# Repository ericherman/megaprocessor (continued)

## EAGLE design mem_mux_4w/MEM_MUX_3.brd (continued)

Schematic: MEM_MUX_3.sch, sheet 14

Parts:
D25, D26, D27, D28, D29, D30, D31, D32: L-1334SRT; LED3MM
Q127, Q128, Q129, Q130, Q131, Q132, Q133, Q134, Q135, Q136, Q137, Q138, Q139, Q140, Q141, Q142: 2N7000; TO92-DGS
R151, R153, R155, R157, R159, R161, R163, R165, R167, R168, R169, R170, R171, R172, R173, R174: 10k; R_P2INCH
R152, R154, R156, R158, R160, R162, R164, R166: 470; R_P2INCH

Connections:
+5V: D25.A, D26.A, D27.A, D28.A, D29.A, D30.A, D31.A, D32.A, R151.2, R153.2, R155.2, R157.2, R159.2, R161.2, R163.2, R165.2, R167.2, R168.2, R169.2, R170.2, R171.2, R172.2, R173.2, R174.2; also elsewhere on the board
CS_3_N: Q128.S, Q130.S, Q132.S, Q134.S, Q136.S, Q138.S, Q140.S, Q142.S; also elsewhere on the board
GND: Q127.S, Q129.S, Q131.S, Q133.S, Q135.S, Q137.S, Q139.S, Q141.S; also elsewhere on the board
unnamed: Q127.D, Q128.G, R151.1, R152.1
unnamed: D25.K (C), R152.2
unnamed: Q129.D, Q130.G, R153.1, R154.1
unnamed: D26.K (C), R154.2
unnamed: Q131.D, Q132.G, R155.1, R156.1
unnamed: D27.K (C), R156.2
unnamed: Q133.D, Q134.G, R157.1, R158.1
unnamed: D28.K (C), R158.2
unnamed: Q135.D, Q136.G, R159.1, R160.1
unnamed: D29.K (C), R160.2
unnamed: Q137.D, Q138.G, R161.1, R162.1
unnamed: D30.K (C), R162.2
unnamed: Q139.D, Q140.G, R163.1, R164.1
unnamed: D31.K (C), R164.2
unnamed: Q141.D, Q142.G, R165.1, R166.1
unnamed: D32.K (C), R166.2
P3_RD0: Q127.G; also elsewhere on the board
P3_RD0_B: Q128.D, R167.1; also elsewhere on the board
P3_RD1: Q129.G; also elsewhere on the board
P3_RD1_B: Q130.D, R168.1; also elsewhere on the board
P3_RD2: Q131.G; also elsewhere on the board
P3_RD2_B: Q132.D, R169.1; also elsewhere on the board
P3_RD3: Q133.G; also elsewhere on the board
P3_RD3_B: Q134.D, R170.1; also elsewhere on the board
P3_RD4: Q135.G; also elsewhere on the board
P3_RD4_B: Q136.D, R171.1; also elsewhere on the board
P3_RD5: Q137.G; also elsewhere on the board
P3_RD5_B: Q138.D, R172.1; also elsewhere on the board
P3_RD6: Q139.G; also elsewhere on the board
P3_RD6_B: Q140.D, R173.1; also elsewhere on the board
P3_RD7: Q141.G; also elsewhere on the board
P3_RD7_B: Q142.D, R174.1; also elsewhere on the board

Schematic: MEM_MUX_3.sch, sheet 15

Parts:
J7, J8: 20_HDR_LOCKING_RA
Q143, Q144: 2N7000; TO92-DGS
R175, R176: 10k; R_P2INCH

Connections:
+5V: R175.2, R176.2; also elsewhere on the board
GND: J7.1, J7.10, J7.11, J7.20, J8.2, J8.4, Q143.S, Q144.S; also elsewhere on the board
P3_A0: J8.5; also elsewhere on the board
P3_A1: J8.6; also elsewhere on the board
P3_A2: J8.7; also elsewhere on the board
P3_A3: J8.8; also elsewhere on the board
P3_A4: J8.9; also elsewhere on the board
P3_A5: J8.10; also elsewhere on the board
P3_A6: J8.11; also elsewhere on the board
P3_A7: J8.12; also elsewhere on the board
P3_A8: J8.13; also elsewhere on the board
P3_A9: J8.14; also elsewhere on the board
P3_A10: J8.15; also elsewhere on the board
P3_A11: J8.16; also elsewhere on the board
P3_A12: J8.17; also elsewhere on the board
P3_A13: J8.18; also elsewhere on the board
P3_A14: J8.19; also elsewhere on the board
P3_A15: J8.20; also elsewhere on the board
P3_CS: Q143.G; also elsewhere on the board
P3_CS_N: J8.1, Q143.D, R175.1
P3_RD0: J7.2; also elsewhere on the board
P3_RD1: J7.3; also elsewhere on the board
P3_RD2: J7.4; also elsewhere on the board
P3_RD3: J7.5; also elsewhere on the board
P3_RD4: J7.6; also elsewhere on the board
P3_RD5: J7.7; also elsewhere on the board
P3_RD6: J7.8; also elsewhere on the board
P3_RD7: J7.9; also elsewhere on the board
P3_WD0: J7.12; also elsewhere on the board
P3_WD1: J7.13; also elsewhere on the board
P3_WD2: J7.14; also elsewhere on the board
P3_WD3: J7.15; also elsewhere on the board
P3_WD4: J7.16; also elsewhere on the board
P3_WD5: J7.17; also elsewhere on the board
P3_WD6: J7.18; also elsewhere on the board
P3_WD7: J7.19; also elsewhere on the board
P3_WE_N: J8.3, Q144.D, R176.1
WE: Q144.G; also elsewhere on the board

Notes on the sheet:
Port 1 data
Port 1 address
rd data
wr_data

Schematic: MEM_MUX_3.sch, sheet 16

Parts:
Q145, Q146, Q147, Q148, Q149, Q150, Q151, Q152, Q153, Q154, Q155, Q156, Q157, Q158, Q159, Q160, Q161, Q162, Q163, Q164, Q165, Q166, Q167, Q168: 2N7000; TO92-DGS
R177, R178, R179, R180, R181, R182, R183, R184, R185, R186, R187, R188, R189, R190, R191, R192, R193, R194, R195, R196, R197, R198, R199, R200: 10k; R_P2INCH

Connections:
+5V: R177.2, R178.2, R179.2, R180.2, R181.2, R182.2, R183.2, R184.2, R185.2, R186.2, R187.2, R188.2, R189.2, R190.2, R191.2, R192.2, R193.2, R194.2, R195.2, R196.2, R197.2, R198.2, R199.2, R200.2; also elsewhere on the board
A0_N: Q153.G; also elsewhere on the board
A1_N: Q154.G; also elsewhere on the board
A2_N: Q155.G; also elsewhere on the board
A3_N: Q156.G; also elsewhere on the board
A4_N: Q157.G; also elsewhere on the board
A5_N: Q158.G; also elsewhere on the board
A6_N: Q159.G; also elsewhere on the board
A7_N: Q160.G; also elsewhere on the board
A8_N: Q161.G; also elsewhere on the board
A9_N: Q162.G; also elsewhere on the board
A10_N: Q163.G; also elsewhere on the board
A11_N: Q164.G; also elsewhere on the board
A12_N: Q165.G; also elsewhere on the board
A13_N: Q166.G; also elsewhere on the board
A14_N: Q167.G; also elsewhere on the board
A15_N: Q168.G; also elsewhere on the board
GND: Q145.S, Q146.S, Q147.S, Q148.S, Q149.S, Q150.S, Q151.S, Q152.S, Q153.S, Q154.S, Q155.S, Q156.S, Q157.S, Q158.S, Q159.S, Q160.S, Q161.S, Q162.S, Q163.S, Q164.S, Q165.S, Q166.S, Q167.S, Q168.S; also elsewhere on the board
P3_A0: Q153.D, R185.1; also elsewhere on the board
P3_A1: Q154.D, R186.1; also elsewhere on the board
P3_A2: Q155.D, R187.1; also elsewhere on the board
P3_A3: Q156.D, R188.1; also elsewhere on the board
P3_A4: Q157.D, R189.1; also elsewhere on the board
P3_A5: Q158.D, R190.1; also elsewhere on the board
P3_A6: Q159.D, R191.1; also elsewhere on the board
P3_A7: Q160.D, R192.1; also elsewhere on the board
P3_A8: Q161.D, R193.1; also elsewhere on the board
P3_A9: Q162.D, R194.1; also elsewhere on the board
P3_A10: Q163.D, R195.1; also elsewhere on the board
P3_A11: Q164.D, R196.1; also elsewhere on the board
P3_A12: Q165.D, R197.1; also elsewhere on the board
P3_A13: Q166.D, R198.1; also elsewhere on the board
P3_A14: Q167.D, R199.1; also elsewhere on the board
P3_A15: Q168.D, R200.1; also elsewhere on the board
P3_WD0: Q145.D, R177.1; also elsewhere on the board
P3_WD1: Q146.D, R178.1; also elsewhere on the board
P3_WD2: Q147.D, R179.1; also elsewhere on the board
P3_WD3: Q148.D, R180.1; also elsewhere on the board
P3_WD4: Q149.D, R181.1; also elsewhere on the board
P3_WD5: Q150.D, R182.1; also elsewhere on the board
P3_WD6: Q151.D, R183.1; also elsewhere on the board
P3_WD7: Q152.D, R184.1; also elsewhere on the board
WD0_N: Q145.G; also elsewhere on the board
WD1_N: Q146.G; also elsewhere on the board
WD2_N: Q147.G; also elsewhere on the board
WD3_N: Q148.G; also elsewhere on the board
WD4_N: Q149.G; also elsewhere on the board
WD5_N: Q150.G; also elsewhere on the board
WD6_N: Q151.G; also elsewhere on the board
WD7_N: Q152.G; also elsewhere on the board

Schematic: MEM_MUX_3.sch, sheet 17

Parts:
D33, D34, D35, D69: L-1334SRT; LED3MM
Q169, Q170, Q171, Q172, Q173, Q174, Q175, Q176, Q177, Q178, Q179, Q180, Q181, Q182, Q183, Q184, Q185, Q186, Q187, Q188: 2N7000; TO92-DGS
R201, R203, R205, R207, R257, R258, R259, R260: 10k; R_P2INCH
R202, R204, R206, R208: 470; R_P2INCH

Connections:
+5V: D33.A, D34.A, D35.A, D69.A, R201.2, R203.2, R205.2, R207.2, R257.2, R258.2, R259.2, R260.2; also elsewhere on the board
GND: Q170.S, Q173.S, Q175.S, Q178.S, Q180.S, Q183.S, Q185.S, Q188.S; also elsewhere on the board
unnamed: Q174.D, Q175.G, R203.1, R204.1
unnamed: D33.K (C), R204.2
unnamed: Q177.S, Q178.D
unnamed: Q176.S, Q177.D
unnamed: Q174.S, Q176.D
unnamed: Q179.D, Q180.G, R205.1, R206.1
unnamed: D34.K (C), R206.2
unnamed: Q182.S, Q183.D
unnamed: Q181.S, Q182.D
unnamed: Q179.S, Q181.D
unnamed: Q184.D, Q185.G, R207.1, R208.1
unnamed: D35.K (C), R208.2
unnamed: Q187.S, Q188.D
unnamed: Q186.S, Q187.D
unnamed: Q184.S, Q186.D
unnamed: Q169.D, Q170.G, R201.1, R202.1
unnamed: D69.K (C), R202.2
unnamed: Q172.S, Q173.D
unnamed: Q171.S, Q172.D
unnamed: Q169.S, Q171.D
P0_RD0_B: Q169.G; also elsewhere on the board
P0_RD1_B: Q174.G; also elsewhere on the board
P0_RD2_B: Q179.G; also elsewhere on the board
P0_RD3_B: Q184.G; also elsewhere on the board
P1_RD0_B: Q171.G; also elsewhere on the board
P1_RD1_B: Q176.G; also elsewhere on the board
P1_RD2_B: Q181.G; also elsewhere on the board
P1_RD3_B: Q186.G; also elsewhere on the board
P2_RD0_B: Q172.G; also elsewhere on the board
P2_RD1_B: Q177.G; also elsewhere on the board
P2_RD2_B: Q182.G; also elsewhere on the board
P2_RD3_B: Q187.G; also elsewhere on the board
P3_RD0_B: Q173.G; also elsewhere on the board
P3_RD1_B: Q178.G; also elsewhere on the board
P3_RD2_B: Q183.G; also elsewhere on the board
P3_RD3_B: Q188.G; also elsewhere on the board
RD0: Q170.D, R257.1; also elsewhere on the board
RD1: Q175.D, R258.1; also elsewhere on the board
RD2: Q180.D, R259.1; also elsewhere on the board
RD3: Q185.D, R260.1; also elsewhere on the board

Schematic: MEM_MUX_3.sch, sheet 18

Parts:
D36, D37, D38, D39: L-1334SRT; LED3MM
Q189, Q190, Q191, Q192, Q193, Q194, Q195, Q196, Q197, Q198, Q199, Q200, Q201, Q202, Q203, Q204, Q205, Q206, Q207, Q208: 2N7000; TO92-DGS
R209, R211, R213, R215, R253, R254, R255, R256: 10k; R_P2INCH
R210, R212, R214, R216: 470; R_P2INCH

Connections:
+5V: D36.A, D37.A, D38.A, D39.A, R209.2, R211.2, R213.2, R215.2, R253.2, R254.2, R255.2, R256.2; also elsewhere on the board
GND: Q190.S, Q193.S, Q195.S, Q198.S, Q200.S, Q203.S, Q205.S, Q208.S; also elsewhere on the board
unnamed: Q189.D, Q190.G, R209.1, R210.1
unnamed: D36.K (C), R210.2
unnamed: Q192.S, Q193.D
unnamed: Q191.S, Q192.D
unnamed: Q189.S, Q191.D
unnamed: Q194.D, Q195.G, R211.1, R212.1
unnamed: D37.K (C), R212.2
unnamed: Q197.S, Q198.D
unnamed: Q196.S, Q197.D
unnamed: Q194.S, Q196.D
unnamed: Q199.D, Q200.G, R213.1, R214.1
unnamed: D38.K (C), R214.2
unnamed: Q202.S, Q203.D
unnamed: Q201.S, Q202.D
unnamed: Q199.S, Q201.D
unnamed: Q204.D, Q205.G, R215.1, R216.1
unnamed: D39.K (C), R216.2
unnamed: Q207.S, Q208.D
unnamed: Q206.S, Q207.D
unnamed: Q204.S, Q206.D
P0_RD4_B: Q189.G; also elsewhere on the board
P0_RD5_B: Q194.G; also elsewhere on the board
P0_RD6_B: Q199.G; also elsewhere on the board
P0_RD7_B: Q204.G; also elsewhere on the board
P1_RD4_B: Q191.G; also elsewhere on the board
P1_RD5_B: Q196.G; also elsewhere on the board
P1_RD6_B: Q201.G; also elsewhere on the board
P1_RD7_B: Q206.G; also elsewhere on the board
P2_RD4_B: Q192.G; also elsewhere on the board
P2_RD5_B: Q197.G; also elsewhere on the board
P2_RD6_B: Q202.G; also elsewhere on the board
P2_RD7_B: Q207.G; also elsewhere on the board
P3_RD4_B: Q193.G; also elsewhere on the board
P3_RD5_B: Q198.G; also elsewhere on the board
P3_RD6_B: Q203.G; also elsewhere on the board
P3_RD7_B: Q208.G; also elsewhere on the board
RD4: Q190.D, R253.1; also elsewhere on the board
RD5: Q195.D, R254.1; also elsewhere on the board
RD6: Q200.D, R255.1; also elsewhere on the board
RD7: Q205.D, R256.1; also elsewhere on the board

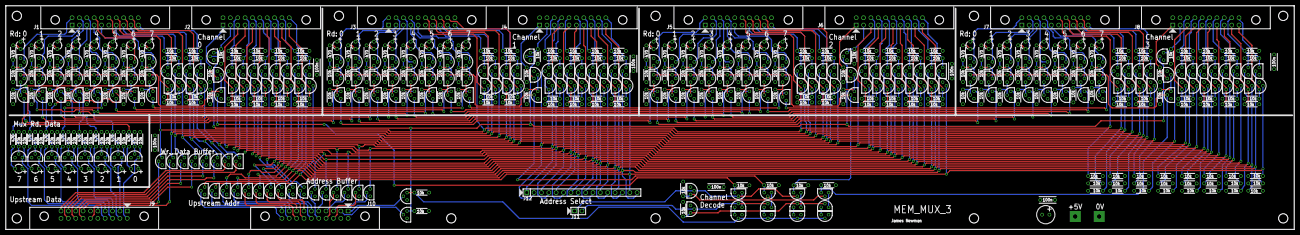
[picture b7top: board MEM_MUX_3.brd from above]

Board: 4 copper layers, 444.5 x 77.1 mm, 584 parts (0 on the bottom side), 354 nets.

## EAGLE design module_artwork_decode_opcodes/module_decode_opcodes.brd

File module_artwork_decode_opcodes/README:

Opcode Decode

This decodes the opcode to work out what the instruction is.

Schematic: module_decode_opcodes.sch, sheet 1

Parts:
CMP13, CMP14, CMP15, CMP17, CMP49: BUS_SPLIT_DISPLAY

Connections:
ADD2_IS_Z: CMP49.P$11 (OUT_10)
ADD2_LSB: CMP49.P$12 (OUT_11)
BUS_H_D: CMP14.INPUT
BUS_INSTR: CMP15.INPUT
BUS_PS: CMP17.INPUT
BUS_RN_ARITH_FLAGS: CMP49.INPUT
BUS_STATE: CMP13.INPUT
FLAG_C: CMP17.P$6 (OUT_5)
FLAG_D: CMP17.P$7 (OUT_6)
FLAG_F0: CMP17.P$9 (OUT_8)
FLAG_F1: CMP17.P$10 (OUT_9)
FLAG_F2: CMP17.P$11 (OUT_10)
FLAG_F3: CMP17.P$12 (OUT_11)
FLAG_F4: CMP17.P$13 (OUT_12)
FLAG_F5: CMP17.P$14 (OUT_13)
FLAG_F6: CMP17.P$15 (OUT_14); also elsewhere on the board
FLAG_I: CMP17.P$1 (OUT_0); also elsewhere on the board
FLAG_N: CMP17.P$2 (OUT_1)
FLAG_V: CMP17.P$4 (OUT_3)
FLAG_X: CMP17.P$5 (OUT_4)
FLAG_Z: CMP17.P$3 (OUT_2)
H_0: CMP14.P$1 (OUT_0); also elsewhere on the board
H_1: CMP14.P$2 (OUT_1); also elsewhere on the board
H_2: CMP14.P$3 (OUT_2); also elsewhere on the board
H_3: CMP14.P$4 (OUT_3); also elsewhere on the board
H_4: CMP14.P$5 (OUT_4); also elsewhere on the board
H_5: CMP14.P$6 (OUT_5)
H_6: CMP14.P$7 (OUT_6); also elsewhere on the board
H_7: CMP14.P$8 (OUT_7); also elsewhere on the board
H_8: CMP14.P$9 (OUT_8)
H_9: CMP14.P$10 (OUT_9)
H_10: CMP14.P$11 (OUT_10)
H_11: CMP14.P$12 (OUT_11)
H_12: CMP14.P$13 (OUT_12)
H_13: CMP14.P$14 (OUT_13)
H_14: CMP14.P$15 (OUT_14)
H_15: CMP14.P$16 (OUT_15)
INSTR_0: CMP15.P$1 (OUT_0); also elsewhere on the board
INSTR_0_N: CMP15.P$9 (OUT_8)
INSTR_1: CMP15.P$2 (OUT_1); also elsewhere on the board
INSTR_1_N: CMP15.P$10 (OUT_9)
INSTR_2: CMP15.P$3 (OUT_2); also elsewhere on the board
INSTR_2_N: CMP15.P$11 (OUT_10); also elsewhere on the board
INSTR_3: CMP15.P$4 (OUT_3); also elsewhere on the board
INSTR_3_N: CMP15.P$12 (OUT_11); also elsewhere on the board
INSTR_4: CMP15.P$5 (OUT_4); also elsewhere on the board
INSTR_4_N: CMP15.P$13 (OUT_12)
INSTR_5: CMP15.P$6 (OUT_5); also elsewhere on the board
INSTR_5_N: CMP15.P$14 (OUT_13)
INSTR_6: CMP15.P$7 (OUT_6); also elsewhere on the board
INSTR_6_N: CMP15.P$15 (OUT_14); also elsewhere on the board
INSTR_7: CMP15.P$8 (OUT_7); also elsewhere on the board
INSTR_7_N: CMP15.P$16 (OUT_15); also elsewhere on the board
MAIN_RN_INPUT_MUX_IS_N: CMP49.P$9 (OUT_8)
MAIN_RN_INPUT_MUX_IS_Z: CMP49.P$10 (OUT_9)
R0_IS_N: CMP49.P$1 (OUT_0)
R0_IS_Z: CMP49.P$5 (OUT_4)
R1_IS_N: CMP49.P$2 (OUT_1)
R1_IS_Z: CMP49.P$6 (OUT_5); also elsewhere on the board
R2_IS_N: CMP49.P$3 (OUT_2)
R2_IS_Z: CMP49.P$7 (OUT_6)
R3_IS_N: CMP49.P$4 (OUT_3)
R3_IS_Z: CMP49.P$8 (OUT_7)
STATE_0: CMP13.P$1 (OUT_0); also elsewhere on the board
STATE_1: CMP13.P$2 (OUT_1); also elsewhere on the board
STATE_2: CMP13.P$3 (OUT_2); also elsewhere on the board
STATE_3: CMP13.P$4 (OUT_3); also elsewhere on the board
STATE_4: CMP13.P$5 (OUT_4)
STATE_5: CMP13.P$6 (OUT_5); also elsewhere on the board
STATE_6: CMP13.P$7 (OUT_6)
STATE_7: CMP13.P$8 (OUT_7); also elsewhere on the board
STATE_8: CMP13.P$9 (OUT_8)
STATE_9: CMP13.P$10 (OUT_9)
STATE_10: CMP13.P$11 (OUT_10)
STATE_11: CMP13.P$12 (OUT_11)
STATE_12: CMP13.P$13 (OUT_12)
STATE_13: CMP13.P$14 (OUT_13)
STATE_14: CMP13.P$15 (OUT_14)
STATE_15: CMP13.P$16 (OUT_15)

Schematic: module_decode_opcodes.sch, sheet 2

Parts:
CMP21, CMP22: DECODER16

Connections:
INSTR_0: CMP22.A0; also elsewhere on the board
INSTR_1: CMP22.A1; also elsewhere on the board
INSTR_2: CMP22.A2; also elsewhere on the board
INSTR_3: CMP22.A3; also elsewhere on the board
INSTR_4: CMP21.A0; also elsewhere on the board
INSTR_5: CMP21.A1; also elsewhere on the board
INSTR_6: CMP21.A2; also elsewhere on the board
INSTR_7: CMP21.A3; also elsewhere on the board
OPCODE_IS_ABSOLUTE_GROUP: CMP21.P11; also elsewhere on the board
OPCODE_IS_ADDQ_GROUP: CMP21.P5; also elsewhere on the board
OPCODE_IS_ADDX: CMP22.P12; also elsewhere on the board
OPCODE_IS_ADD_GROUP: CMP21.P4; also elsewhere on the board
OPCODE_IS_ADD_SP: CMP22.P6; also elsewhere on the board
OPCODE_IS_ANDI_PS: CMP22.P4; also elsewhere on the board
OPCODE_IS_AND_GROUP: CMP21.P1; also elsewhere on the board
OPCODE_IS_BRANCH_GROUP: CMP21.P14; also elsewhere on the board
OPCODE_IS_CMP_GROUP: CMP21.P7; also elsewhere on the board
OPCODE_IS_DIVS: CMP22.P11; also elsewhere on the board
OPCODE_IS_DIVU: CMP22.P10; also elsewhere on the board
OPCODE_IS_IMMEDIATE_GROUP: CMP21.P13; also elsewhere on the board
OPCODE_IS_INDIRECT_GROUP: CMP21.P8; also elsewhere on the board
OPCODE_IS_JMP_ABS: CMP22.P3; also elsewhere on the board
OPCODE_IS_JMP_R0: CMP22.P2; also elsewhere on the board
OPCODE_IS_MISC_GROUP: CMP21.P15, CMP22.E
OPCODE_IS_MOVER_GROUP: CMP21.P0
OPCODE_IS_MOVE_R0_SP: CMP22.P0; also elsewhere on the board
OPCODE_IS_MOVE_SP_R0: CMP22.P1; also elsewhere on the board
OPCODE_IS_MULS: CMP22.P9; also elsewhere on the board
OPCODE_IS_MULU: CMP22.P8; also elsewhere on the board
OPCODE_IS_NEGX: CMP22.P14; also elsewhere on the board
OPCODE_IS_NOP_1: CMP22.P15; also elsewhere on the board
OPCODE_IS_ORI_PS: CMP22.P5; also elsewhere on the board
OPCODE_IS_OR_GROUP: CMP21.P3; also elsewhere on the board
OPCODE_IS_POSTINC_GROUP: CMP21.P9; also elsewhere on the board
OPCODE_IS_SQRT: CMP22.P7; also elsewhere on the board
OPCODE_IS_STACK_GROUP: CMP21.P12; also elsewhere on the board
OPCODE_IS_STACK_REL_GROUP: CMP21.P10; also elsewhere on the board
OPCODE_IS_SUBX: CMP22.P13; also elsewhere on the board
OPCODE_IS_SUB_GROUP: CMP21.P6; also elsewhere on the board
OPCODE_IS_XOR_GROUP: CMP21.P2; also elsewhere on the board

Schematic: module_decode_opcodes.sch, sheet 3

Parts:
CMP59, CMP60: DECODER16

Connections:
INSTR_0: CMP59.A0; also elsewhere on the board
INSTR_1: CMP59.A1; also elsewhere on the board
INSTR_2: CMP59.A2; also elsewhere on the board
INSTR_3: CMP59.A3; also elsewhere on the board
INSTR_4: CMP60.A0; also elsewhere on the board
INSTR_5: CMP60.A1; also elsewhere on the board
INSTR_6: CMP60.A2; also elsewhere on the board
INSTR_7_N: CMP60.E; also elsewhere on the board
OPCODE_IS_ABS: CMP60.P15; also elsewhere on the board
OPCODE_IS_AND: CMP60.P1
OPCODE_IS_CMP: CMP60.P7; also elsewhere on the board
OPCODE_IS_INV: CMP60.P11; also elsewhere on the board
OPCODE_IS_JSR_ABS: CMP59.P15; also elsewhere on the board
OPCODE_IS_JSR_R0: CMP59.P14; also elsewhere on the board
OPCODE_IS_MOVER: CMP60.P0; also elsewhere on the board
OPCODE_IS_NEG: CMP60.P14; also elsewhere on the board
OPCODE_IS_NOP_2: CMP59.P5; also elsewhere on the board
OPCODE_IS_OR: CMP60.P3; also elsewhere on the board
OPCODE_IS_POP_PS: CMP59.P4; also elsewhere on the board
OPCODE_IS_PUSH_PS: CMP59.P12; also elsewhere on the board
OPCODE_IS_RET: CMP59.P6; also elsewhere on the board
OPCODE_IS_RETI: CMP59.P7; also elsewhere on the board
OPCODE_IS_STACK_GROUP: CMP59.E; also elsewhere on the board
OPCODE_IS_SUB: CMP60.P6; also elsewhere on the board
OPCODE_IS_SXT: CMP60.P8; also elsewhere on the board
OPCODE_IS_TEST: CMP60.P9; also elsewhere on the board
OPCODE_IS_TRAP: CMP59.P13; also elsewhere on the board
RA_EQUALS_RB: CMP60.A3; also elsewhere on the board

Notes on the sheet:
alu_select_enable = ~bus_f_instr.instr[7];
alu_select[0] = bus_f_instr.instr[4]; alu_select[1] = bus_f_instr.instr[5]; alu_select[2] = bus_f_instr.instr[6]; alu_select[3] = RA_equals_RB;

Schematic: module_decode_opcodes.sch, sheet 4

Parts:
CMP1, CMP2: XOR
CMP3, CMP69, CMP72: 2AND
CMP23: 2OR
CMP67, CMP94: DECODER4

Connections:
INSTR_0: CMP1.P$1 (A1); also elsewhere on the board
INSTR_1: CMP2.P$1 (A1); also elsewhere on the board
INSTR_2: CMP1.P$2 (A2), CMP67.A0, CMP94.A0; also elsewhere on the board
INSTR_3: CMP2.P$2 (A2), CMP67.A1, CMP72.P$1 (1), CMP94.A1; also elsewhere on the board
INSTR_3_N: CMP69.P$1 (1); also elsewhere on the board
INSTR_6: CMP23.P$2 (A1); also elsewhere on the board
INSTR_7: CMP23.P$1 (A2); also elsewhere on the board
unnamed: CMP1.OUT_N (N), CMP3.P$2 (2)
unnamed: CMP2.OUT_N (N), CMP3.P$1 (1)
OPCODE_IS_BIT_XX: CMP67.P3; also elsewhere on the board
OPCODE_IS_BIT_XX_N: CMP67.N3; also elsewhere on the board
OPCODE_IS_IMMEDIATE_GROUP: CMP67.E, CMP69.P$2 (2), CMP72.P$2 (2); also elsewhere on the board
OPCODE_IS_LDI_X: CMP69.OUT_P; also elsewhere on the board
OPCODE_IS_LOGIC_GROUP: CMP23.OUT_M (N); also elsewhere on the board
OPCODE_IS_POP_RA: CMP94.P0; also elsewhere on the board
OPCODE_IS_PUSH_RA: CMP94.P2; also elsewhere on the board
OPCODE_IS_SHIFT_BIT: CMP72.OUT_P; also elsewhere on the board
OPCODE_IS_SHIFT_XX: CMP67.P2; also elsewhere on the board
OPCODE_IS_STACK_GROUP: CMP94.E; also elsewhere on the board
RA_EQUALS_RB: CMP3.OUT_P; also elsewhere on the board
RA_EQUALS_RB_N: CMP3.OUT_M (N)

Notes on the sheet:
RA0_equals_RB0 = ~Cpnt_XOR(RA_bits.Output()[0], RB_bits.Output()[0]); RA1_equals_RB1 = ~Cpnt_XOR(RA_bits.Output()[1], RB_bits.Output()[1]); RA_equals_RB = Cpnt_2AND(RA0_equals_RB0,RA1_equals_RB1);
opcode_is_logic_group = ~Cpnt_2OR(bus_f_instr.instr[7], bus_f_instr.instr[6]);
opcode_is_pop_ra = stack_decode.Output()[0]; opcode_is_push_ra = stack_decode.Output()[2];
opcode_is_ldi_x = Cpnt_2AND(opcode_is_immediate_group, ~bus_f_instr.instr[3]);
opcode_is_shift_bit = Cpnt_2AND(opcode_is_immediate_group, bus_f_instr.instr[3]);
opcode_is_shift_xx = immediate_decode.Output()[2]; opcode_is_bit_xx = immediate_decode.Output()[3];

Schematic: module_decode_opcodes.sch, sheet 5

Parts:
CMP4, CMP5, CMP75, CMP76: 2OR
CMP74, CMP77: 3OR
CMP82: DECODER4

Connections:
BIT_SHIFT_MODE__CHANGE__ARITH: CMP82.P1; also elsewhere on the board
BIT_SHIFT_MODE__CLEAR__ROT: CMP82.P2
BIT_SHIFT_MODE__CLEAR__ROT_N: CMP82.N2; also elsewhere on the board
BIT_SHIFT_MODE__SET__X_ROT: CMP82.P3; also elsewhere on the board
BIT_SHIFT_MODE__TEST: CMP82.P0
BIT_SHIFT_MODE__TEST_N: CMP82.N0; also elsewhere on the board
H_6: CMP82.A0; also elsewhere on the board
H_7: CMP82.A1; also elsewhere on the board
OPCODE_IS_ADDX: CMP74.P$1 (0); also elsewhere on the board
OPCODE_IS_DIV: CMP76.OUT_P, CMP77.P$1 (0); also elsewhere on the board
OPCODE_IS_DIVS: CMP76.P$2 (A1); also elsewhere on the board
OPCODE_IS_DIVU: CMP76.P$1 (A2); also elsewhere on the board
OPCODE_IS_JSR_ABS: CMP5.P$1 (A2); also elsewhere on the board
OPCODE_IS_JSR_R0: CMP5.P$2 (A1); also elsewhere on the board
OPCODE_IS_JSR_X: CMP5.OUT_P; also elsewhere on the board
OPCODE_IS_MUL: CMP75.OUT_P, CMP77.P$3 (2)
OPCODE_IS_MULS: CMP75.P$2 (A1); also elsewhere on the board
OPCODE_IS_MULU: CMP75.P$1 (A2); also elsewhere on the board
OPCODE_IS_MUL_N: CMP75.OUT_M (N); also elsewhere on the board
OPCODE_IS_MUL_SQRT_DIV: CMP77.OUT_P; also elsewhere on the board
OPCODE_IS_NEGX: CMP74.P$3 (2); also elsewhere on the board
OPCODE_IS_NOP: CMP4.OUT_P; also elsewhere on the board
OPCODE_IS_NOP_1: CMP4.P$2 (A1); also elsewhere on the board
OPCODE_IS_NOP_2: CMP4.P$1 (A2); also elsewhere on the board
OPCODE_IS_SQRT: CMP77.P$2 (1); also elsewhere on the board
OPCODE_IS_SUBX: CMP74.P$2 (1); also elsewhere on the board
OPCODE_IS_X_ARITH: CMP74.OUT_P; also elsewhere on the board

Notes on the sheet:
opcode_is_x_arith = Cpnt_3OR(opcode_is_addx, opcode_is_subx, opcode_is_negx);
opcode_is_mul = Cpnt_2OR(opcode_is_muls, opcode_is_mulu);
opcode_is_div = Cpnt_2OR(opcode_is_divs, opcode_is_divu);
opcode_is_mul_sqrt_div = Cpnt_3OR(opcode_is_mul, opcode_is_sqrt, opcode_is_div);
opcode_is_jsr_x = Cpnt_2OR(opcode_is_jsr_abs,opcode_is_jsr_r0);

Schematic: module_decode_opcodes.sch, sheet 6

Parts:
CMP20: 5OR
CMP24: 3AND
CMP30, CMP62: 4AND
CMP36: 2OR
CMP38: 2AND

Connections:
DIV_BY_ZERO: CMP38.OUT_P; also elsewhere on the board
DIV_BY_ZERO_N: CMP38.OUT_M (N); also elsewhere on the board
FLAG_F6: CMP62.P$3 (2); also elsewhere on the board
H_0: CMP20.1 (0), CMP30.P$4 (3); also elsewhere on the board
H_1: CMP20.2 (1), CMP30.P$3 (2); also elsewhere on the board
H_2: CMP20.3 (2), CMP30.P$2 (1); also elsewhere on the board
H_3: CMP20.4 (3), CMP30.P$1 (0); also elsewhere on the board
H_4: CMP20.5 (4); also elsewhere on the board
H_COUNT_IS_15: CMP30.OUT_P; also elsewhere on the board
LOAD_WEIGHT: CMP62.OUT_P; also elsewhere on the board
OPCODE_IS_DIV: CMP38.P$2 (2); also elsewhere on the board
OPCODE_IS_INDIRECT_GROUP: CMP36.P$1 (A2); also elsewhere on the board
OPCODE_IS_INDIRECT_POSTINC: CMP36.OUT_P; also elsewhere on the board
OPCODE_IS_POSTINC_GROUP: CMP36.P$2 (A1); also elsewhere on the board
OPCODE_IS_SHIFT_XX: CMP24.P$2 (2), CMP62.P$2 (1); also elsewhere on the board
R1_IS_Z: CMP38.P$1 (1); also elsewhere on the board
SHIFT_IS_SHIFTING: CMP24.OUT_P; also elsewhere on the board
SHIFT_VAL_NON_ZERO: CMP20.OUT_P, CMP24.P$3 (3); also elsewhere on the board
SHIFT_VAL_NON_ZERO_N: CMP20.OUT_M (N), CMP62.P$4 (3); also elsewhere on the board
STATE_2: CMP24.P$1 (1), CMP62.P$1 (0); also elsewhere on the board

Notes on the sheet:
h_count_is_15 = Cpnt_4AND(bus_H[3], bus_H[2], bus_H[1], bus_H[0]); //? use bit decode...cannot for sqrt
div_by_zero = Cpnt_2AND(opcode_is_div, bus_rn_arith_flags.r1_is_z);
shift_is_shifting = Cpnt_3AND(opcode_is_shift_xx, bus_state[2], shift_val_non_zero);
load_weight = Cpnt_4AND(opcode_is_shift_xx, bus_state[2], ~shift_val_non_zero, bus_PS[WiC_PS_FLAG_INDEX_F6]);
shift_val_non_zero = Cpnt_5OR(bus_H[4], bus_H[3], bus_H[2], bus_H[1], bus_H[0]);
opcode_is_indirect_postinc = Cpnt_2OR(opcode_is_indirect_group, opcode_is_postinc_group);

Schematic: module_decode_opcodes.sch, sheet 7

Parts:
CMP10, CMP27: 2AND
CMP12, CMP31: 5OR
CMP25: 2OR
CMP26: 2X2AND_OR
CMP39: 3AND

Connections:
END_OF_DATA_TRANSFER: CMP25.OUT_P, CMP26.P$2 (A1), CMP26.P$3 (B0)
EXTERNAL_INTERRUPT: CMP39.P$2 (2)
FLAG_I: CMP39.P$1 (1); also elsewhere on the board
INSTR_7_N: CMP31.4 (3); also elsewhere on the board
IS_END: CMP10.P$2 (2), CMP31.OUT_P, CMP39.P$3 (3); also elsewhere on the board
IS_END_N: CMP31.OUT_M (N); also elsewhere on the board
IS_END__SET_A: CMP26.OUT_P, CMP31.5 (4)
IS_NOT_INTERRUPTING_END: CMP10.OUT_P; also elsewhere on the board
IS_SIMPLE_DATA_TRANSFER: CMP12.OUT_P, CMP26.P$4 (B1); also elsewhere on the board
OPCODE_IS_INDIRECT_POSTINC: CMP12.3 (2); also elsewhere on the board
OPCODE_IS_NOP: CMP31.2 (1); also elsewhere on the board
OPCODE_IS_POP_PS: CMP12.4 (3); also elsewhere on the board
OPCODE_IS_POP_RA: CMP12.2 (1); also elsewhere on the board
OPCODE_IS_PUSH_PS: CMP12.5 (4); also elsewhere on the board
OPCODE_IS_PUSH_RA: CMP12.1 (0); also elsewhere on the board
OPCODE_IS_STACK_REL_GROUP: CMP26.P$1 (A0); also elsewhere on the board
OPCODE_IS_TRAP: CMP27.P$2 (2); also elsewhere on the board
OPCODE_IS_X_ARITH: CMP31.3 (2); also elsewhere on the board
STATE_3: CMP31.1 (0); also elsewhere on the board
STATE_5: CMP25.P$1 (A2); also elsewhere on the board
STATE_7: CMP25.P$2 (A1), CMP27.P$1 (1); also elsewhere on the board
TAKE_INTERRUPT: CMP39.OUT_P; also elsewhere on the board
TAKE_INTERRUPT_N: CMP10.P$1 (1), CMP39.OUT_M (M)
TRAP_STATE_7: CMP27.OUT_P; also elsewhere on the board

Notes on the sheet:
end_of_data_transfer = Cpnt_2OR(bus_state[5], bus_state[7]);
is_end__set_A = Cpnt_2x2AND_OR(end_of_data_transfer, is_simple_data_transfer, end_of_data_transfer, opcode_is_stack_rel_group);
is_end = Cpnt_8OR( is_end__set_A, bus_state[3], is_simple_reg_to_reg, opcode_is_nop, opcode_is_nop_x, opcode_is_x_arith, BIT_VAL_0,BIT_VAL_0);
trap_state_7 = Cpnt_2AND(bus_state[7], opcode_is_trap);
take_interrupt = Cpnt_3AND(is_end, external_interrupt, bus_PS[WiC_PS_FLAG_INDEX_I]);
is_not_interrupting_end = Cpnt_2AND(is_end, ~take_interrupt);

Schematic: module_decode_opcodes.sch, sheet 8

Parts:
CMP9: 2X3AND_OR
CMP28: 2AND
CMP29: 4OR

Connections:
INSTR_2: CMP9.P$5 (B1); also elsewhere on the board
INSTR_2_N: CMP9.P$1 (A0); also elsewhere on the board
INSTR_6_N: CMP28.P$1 (1); also elsewhere on the board
INSTR_7: CMP28.P$2 (2); also elsewhere on the board
LDI_X_STATE_0_BYTE_1_WORD: CMP9.OUT_P; also elsewhere on the board
OPCODE_IS_LDI_X: CMP9.P$2 (A1), CMP9.P$4 (B0), CMP29.1 (0); also elsewhere on the board
OPCODE_IS_LD_ST: CMP29.OUT_P; also elsewhere on the board
OPCODE_IS_LD_ST_SIMPLE: CMP28.OUT_P, CMP29.3 (2)
OPCODE_IS_POP_RA: CMP29.4 (3); also elsewhere on the board
OPCODE_IS_PUSH_RA: CMP29.2 (1); also elsewhere on the board
STATE_0: CMP9.P$6 (B2); also elsewhere on the board
STATE_1: CMP9.P$3 (A2); also elsewhere on the board

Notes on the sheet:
ldi_x_state_0_byte_1_word = Cpnt_2x3AND_OR(bus_state[0], size_bit_is_byte, opcode_is_ldi_x, bus_state[1], size_bit_is_word, opcode_is_ldi_x);
opcode_is_move_r0_sp_state_0 = Cpnt_2AND(opcode_is_move_r0_sp, bus_state[0]);
opcode_is_ld_st_simple = Cpnt_2AND(bus_f_instr.instr[7], ~bus_f_instr.instr[6]);
opcode_is_ld_st = Cpnt_4OR(opcode_is_ld_st_simple, opcode_is_pop_ra, opcode_is_push_ra, opcode_is_ldi_x);

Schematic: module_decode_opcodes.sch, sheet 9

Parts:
CMP6, CMP7: BUS_CONSTRUCT_DISPLAY; BUS_SPLIT_DISPLAY

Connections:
OPCODE_IS_ABSOLUTE_GROUP: CMP6.P$5 (IN_4); also elsewhere on the board
OPCODE_IS_ADDQ_GROUP: CMP6.P$11 (IN_10); also elsewhere on the board
OPCODE_IS_ADDX: CMP7.P$3 (IN_2); also elsewhere on the board
OPCODE_IS_ADD_GROUP: CMP6.P$12 (IN_11); also elsewhere on the board
OPCODE_IS_ADD_SP: CMP7.P$10 (IN_9); also elsewhere on the board
OPCODE_IS_ANDI_PS: CMP7.P$12 (IN_11); also elsewhere on the board
OPCODE_IS_AND_GROUP: CMP6.P$15 (IN_14); also elsewhere on the board
OPCODE_IS_BRANCH_GROUP: CMP6.P$3 (IN_2); also elsewhere on the board
OPCODE_IS_CMP_GROUP: CMP6.P$9 (IN_8); also elsewhere on the board
OPCODE_IS_DIV: CMP7.P$4 (IN_3); also elsewhere on the board
OPCODE_IS_DIVS: CMP7.P$5 (IN_4); also elsewhere on the board
OPCODE_IS_INDIRECT_GROUP: CMP6.P$8 (IN_7); also elsewhere on the board
OPCODE_IS_INDIRECT_POSTINC: CMP6.P$1 (IN_0); also elsewhere on the board
OPCODE_IS_JMP_ABS: CMP7.P$13 (IN_12); also elsewhere on the board
OPCODE_IS_JMP_R0: CMP7.P$14 (IN_13); also elsewhere on the board
OPCODE_IS_LOGIC_GROUP: CMP6.P$2 (IN_1); also elsewhere on the board
OPCODE_IS_MOVE_R0_SP: CMP7.P$16 (IN_15); also elsewhere on the board
OPCODE_IS_MOVE_SP_R0: CMP7.P$15 (IN_14); also elsewhere on the board
OPCODE_IS_MULS: CMP7.P$8 (IN_7); also elsewhere on the board
OPCODE_IS_MULU: CMP7.P$7 (IN_6); also elsewhere on the board
OPCODE_IS_MUL_N: CMP7.P$6 (IN_5); also elsewhere on the board
OPCODE_IS_NEGX: CMP7.P$1 (IN_0); also elsewhere on the board
OPCODE_IS_ORI_PS: CMP7.P$11 (IN_10); also elsewhere on the board
OPCODE_IS_OR_GROUP: CMP6.P$13 (IN_12); also elsewhere on the board
OPCODE_IS_POSTINC_GROUP: CMP6.P$7 (IN_6); also elsewhere on the board
OPCODE_IS_SQRT: CMP7.P$9 (IN_8); also elsewhere on the board
OPCODE_IS_STACK_GROUP: CMP6.P$4 (IN_3); also elsewhere on the board
OPCODE_IS_STACK_REL_GROUP: CMP6.P$6 (IN_5); also elsewhere on the board
OPCODE_IS_SUBX: CMP7.P$2 (IN_1); also elsewhere on the board
OPCODE_IS_SUB_GROUP: CMP6.P$10 (IN_9); also elsewhere on the board
OPCODE_IS_XOR_GROUP: CMP6.P$14 (IN_13); also elsewhere on the board

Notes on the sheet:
clBit opcode_is_indirect_postinc; // 0 clBit opcode_is_logic_group; // 1 clBit opcode_is_branch_group; // 2 clBit opcode_is_stack_group; // 3 clBit opcode_is_absolute_group; // 4 clBit opcode_is_stack_rel_group; // 5 clBit opcode_is_postinc_group; // 6 clBit opcode_is_indirect_group; // 7 clBit opc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
clBit opcode_is_negx; // 0 clBit opcode_is_subx; // 1 clBit opcode_is_addx; // 2 clBit opcode_is_div; // 3 clBit opcode_is_divs; // 4 clBit opcode_is_mul_n; // 5 clBit opcode_is_mul; // 6 clBit opcode_is_muls; // 7 clBit opcode_is_sqrt; // 8 clBit opcode_is_add_sp; // 9 clBit opcode_is_ori_ps; // 1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

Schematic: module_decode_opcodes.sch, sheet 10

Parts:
CMP8, CMP81: BUS_CONSTRUCT_DISPLAY; BUS_SPLIT_DISPLAY

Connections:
BIT_SHIFT_MODE__CHANGE__ARITH: CMP8.P$7 (IN_6); also elsewhere on the board
BIT_SHIFT_MODE__CLEAR__ROT_N: CMP8.P$9 (IN_8); also elsewhere on the board
BIT_SHIFT_MODE__SET__X_ROT: CMP8.P$8 (IN_7); also elsewhere on the board
BIT_SHIFT_MODE__TEST_N: CMP8.P$6 (IN_5); also elsewhere on the board
BUS_ALU_AB: CMP81.INPUT (OUT)
BUS_STK_IMM_AB: CMP8.INPUT (OUT)
DIV_BY_ZERO: CMP81.P$12 (IN_11); also elsewhere on the board
DIV_BY_ZERO_N: CMP81.P$13 (IN_12); also elsewhere on the board
OPCODE_IS_ABS: CMP81.P$4 (IN_3); also elsewhere on the board
OPCODE_IS_BIT_XX: CMP8.P$3 (IN_2); also elsewhere on the board
OPCODE_IS_BIT_XX_N: CMP8.P$4 (IN_3); also elsewhere on the board
OPCODE_IS_CMP: CMP81.P$3 (IN_2); also elsewhere on the board
OPCODE_IS_INV: CMP81.P$8 (IN_7); also elsewhere on the board
OPCODE_IS_JSR_ABS: CMP8.P$10 (IN_9); also elsewhere on the board
OPCODE_IS_JSR_R0: CMP8.P$11 (IN_10); also elsewhere on the board
OPCODE_IS_LDI_X: CMP8.P$1 (IN_0); also elsewhere on the board
OPCODE_IS_MOVER: CMP81.P$10 (IN_9); also elsewhere on the board
OPCODE_IS_MUL_SQRT_DIV: CMP81.P$1 (IN_0); also elsewhere on the board
OPCODE_IS_NEG: CMP81.P$6 (IN_5); also elsewhere on the board
OPCODE_IS_NOP: CMP81.P$14 (IN_13); also elsewhere on the board
OPCODE_IS_OR: CMP81.P$7 (IN_6); also elsewhere on the board
OPCODE_IS_POP_PS: CMP8.P$16 (IN_15); also elsewhere on the board
OPCODE_IS_POP_RA: CMP81.P$15 (IN_14); also elsewhere on the board
OPCODE_IS_PUSH_PS: CMP8.P$13 (IN_12); also elsewhere on the board
OPCODE_IS_PUSH_RA: CMP81.P$16 (IN_15); also elsewhere on the board
OPCODE_IS_RET: CMP8.P$15 (IN_14); also elsewhere on the board
OPCODE_IS_RETI: CMP8.P$14 (IN_13); also elsewhere on the board
OPCODE_IS_SHIFT_BIT: CMP8.P$5 (IN_4); also elsewhere on the board
OPCODE_IS_SHIFT_XX: CMP8.P$2 (IN_1); also elsewhere on the board
OPCODE_IS_SUB: CMP81.P$5 (IN_4); also elsewhere on the board
OPCODE_IS_SXT: CMP81.P$11 (IN_10); also elsewhere on the board
OPCODE_IS_TEST: CMP81.P$9 (IN_8); also elsewhere on the board
OPCODE_IS_TRAP: CMP8.P$12 (IN_11); also elsewhere on the board
OPCODE_IS_X_ARITH: CMP81.P$2 (IN_1); also elsewhere on the board

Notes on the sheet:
clBit opcode_is_ldi_x; // 0 clBit opcode_is_shift_xx; // 1 clBit opcode_is_bit_xx; // 2 clBit opcode_is_bit_xx_n; // 3 clBit opcode_is_shift_bit; // 4 clBit bit_shift_mode_test_n; // 5 clBit bit_shift_mode_arith; // 6 clBit bit_shift_mode_x_rot; // 7 clBit bit_shift_mode_rot_n; // 8 clBit opcode_is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
clBit opcode_is_mul_sqrt_div; // 0 clBit opcode_is_x_arith; // 1 clBit opcode_is_cmp; // 2 clBit opcode_is_abs; // 3 clBit opcode_is_sub; // 4 clBit opcode_is_neg; // 5 clBit opcode_is_or; // 6 clBit opcode_is_inv; // 7 clBit opcode_is_test; // 8 clBit opcode_is_mover; // 9 clBit opcode_is_sxt; // 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

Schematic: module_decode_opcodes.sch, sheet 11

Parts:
CMP91: BUS_CONSTRUCT_DISPLAY; BUS_SPLIT_DISPLAY

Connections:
BUS_SHARED_AB: CMP91.INPUT (OUT)
H_COUNT_IS_15: CMP91.P$3 (IN_2); also elsewhere on the board
IS_END: CMP91.P$11 (IN_10); also elsewhere on the board
IS_END_N: CMP91.P$12 (IN_11); also elsewhere on the board
IS_NOT_INTERRUPTING_END: CMP91.P$14 (IN_13); also elsewhere on the board
IS_SIMPLE_DATA_TRANSFER: CMP91.P$13 (IN_12); also elsewhere on the board
LDI_X_STATE_0_BYTE_1_WORD: CMP91.P$9 (IN_8); also elsewhere on the board
LOAD_WEIGHT: CMP91.P$5 (IN_4); also elsewhere on the board
unnamed: CMP91.P$15 (IN_14), CMP91.P$16 (IN_15)
OPCODE_IS_JSR_X: CMP91.P$10 (IN_9); also elsewhere on the board
OPCODE_IS_LD_ST: CMP91.P$8 (IN_7); also elsewhere on the board
SHIFT_IS_SHIFTING: CMP91.P$4 (IN_3); also elsewhere on the board
SHIFT_VAL_NON_ZERO: CMP91.P$1 (IN_0); also elsewhere on the board
SHIFT_VAL_NON_ZERO_N: CMP91.P$2 (IN_1); also elsewhere on the board
TAKE_INTERRUPT: CMP91.P$7 (IN_6); also elsewhere on the board
TRAP_STATE_7: CMP91.P$6 (IN_5); also elsewhere on the board

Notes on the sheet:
clBit shift_val_non_zero; // 0 clBit shift_val_non_zero_n; // 1 clBit h_count_is_15; // 2 clBit shift_is_shifting; // 3 clBit load_weight; // 4 clBit trap_state_7; // 5 clBit take_interrupt; // 6 clBit opcode_is_ld_st; // 7 clBit ldi_x_state_0_byte_1_word; // 8 clBit opcode_is_jsr_x; // 9 clBit is_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

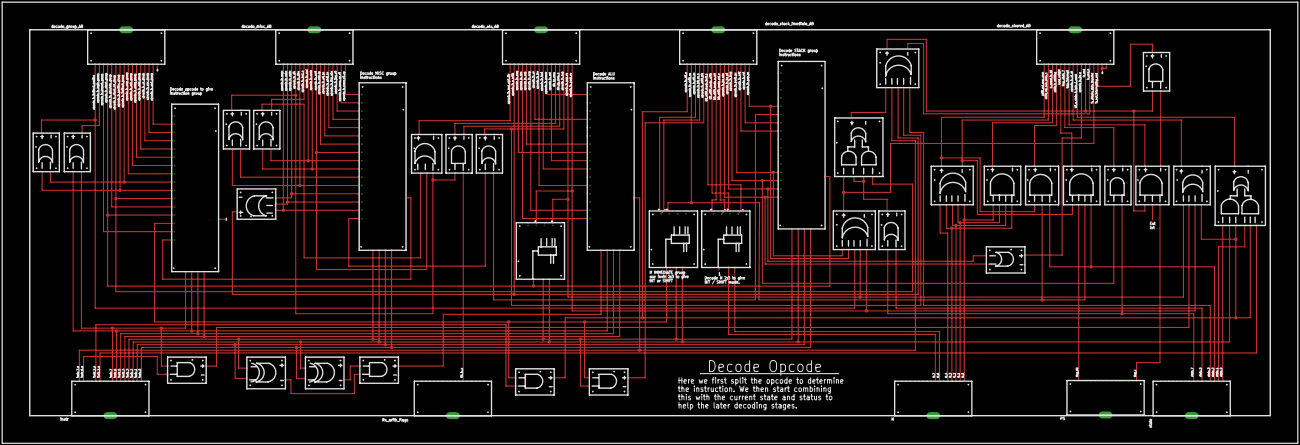
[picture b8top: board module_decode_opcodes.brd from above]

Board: 2 copper layers, 1193.8 x 406.4 mm, 45 parts (0 on the bottom side), 119 nets.

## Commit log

2017-05-20 init
2017-05-20 import from http://www.megaprocessor.com/construction.html
